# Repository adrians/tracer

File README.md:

# Electronic tracer

## The "driver-v1" folder

* Use it for physical tracer board, version 1.
* Prerequisites: `libudev1` and `g++` installed (`sudo apt-get install libudev1 build-essential`).
* Driver based on Kerry Wong's library (<https://github.com/kerrydwong/MCP2210-Library>).
* To build the driver-application, run `cd driver-v1; make`. It will generate the `tracer` binary, which should be run as root (or with the `setuid` bit set).

## The "driver-mock" folder

* Use it for local testing, without a tracer board. It's a dummy data source.
* Prerequisites: `g++` installed.
* To build it, run `cd driver-mock; make`. It will generate the `tracer` binary.

## The "frontend" directory

* Frontend done using electron.js and apex charts.
* It uses `npm`.
* To build, run `npm install`.
* To run, copy the `tracer` binary (from either `driver-v1` or `driver-mock` directories), and then run `npm start`.
* Tested with node 14.x.

The `driver-v1` requires setuid permissions. See the snippet below.

```bash
cd frontend
cp ../driver-v1/tracer .
sudo chown root tracer
sudo chmod +s tracer
npm start
```

## The "board" directory

* Contains the kicad project used for manufacturing the first iteration of the board.

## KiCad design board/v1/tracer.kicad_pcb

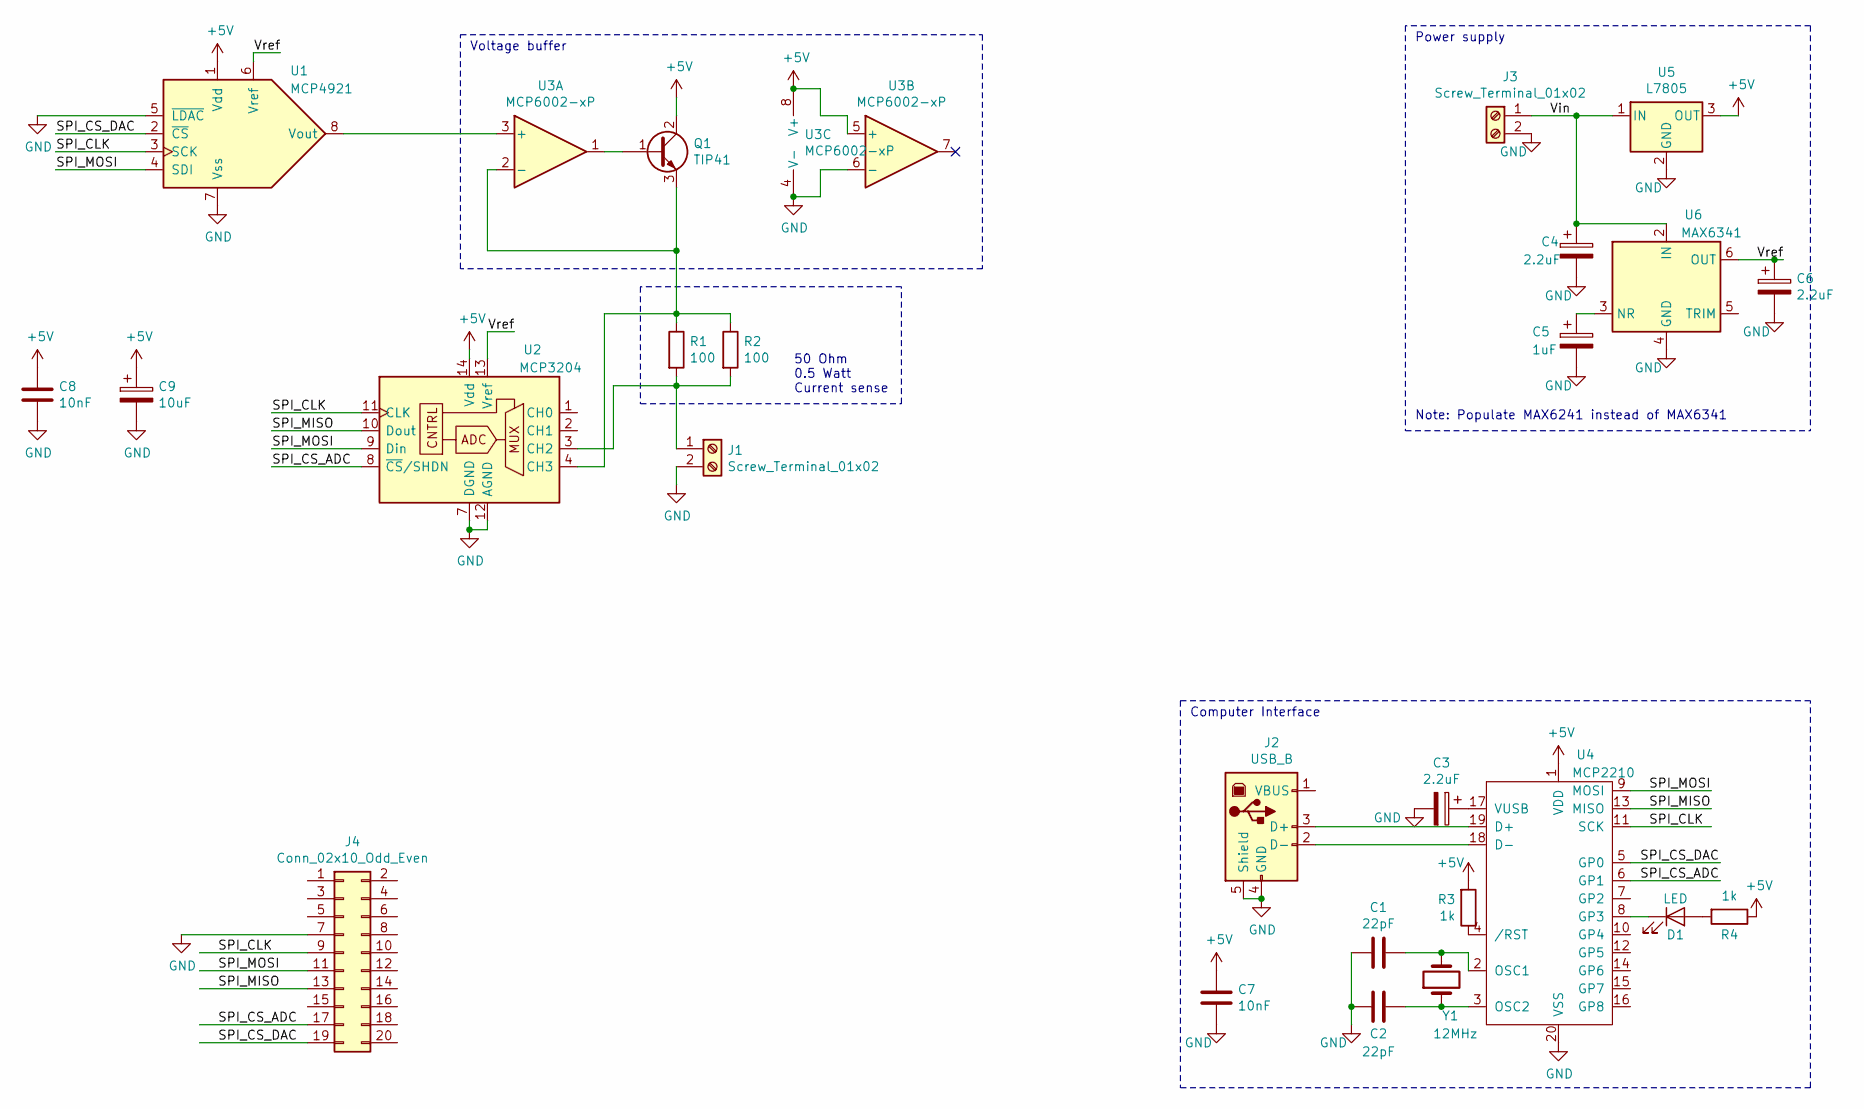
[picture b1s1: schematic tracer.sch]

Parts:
C1, C2: 22pF; C_Disc_D3.0mm_W1.6mm_P2.50mm
C3, C4, C6: 2.2uF; CP_Radial_D4.0mm_P2.00mm
C5: 1uF; CP_Radial_D4.0mm_P2.00mm
C7, C8: 10nF; C_Disc_D3.0mm_W1.6mm_P2.50mm
C9: 10uF; CP_Radial_D4.0mm_P1.50mm
D1: LED; LED_D5.0mm
J1, J3: Screw_Terminal_01x02; TerminalBlock_Phoenix_MKDS-3-2-5.08_1x02_P5.08mm_Horizontal
J2: USB_B; USB_B_OST_USB-B1HSxx_Horizontal
J4: Conn_02x10_Odd_Even; PinHeader_2x10_P2.54mm_Vertical
Q1: TIP41; TO-220-3_Horizontal_TabDown
R1, R2: 100; R_Axial_DIN0207_L6.3mm_D2.5mm_P7.62mm_Horizontal
R3, R4: 1k; R_Axial_DIN0207_L6.3mm_D2.5mm_P7.62mm_Horizontal
U1: MCP4921; DIP-8_W7.62mm
U2: MCP3204; DIP-14_W7.62mm
U3: MCP6002-xP; DIP-8_W7.62mm
U4: MCP2210; SOIC-20W_7.5x12.8mm_P1.27mm
U5: L7805; TO-220-3_Horizontal_TabDown
U6: MAX6341; DIP-8_W7.62mm
Y1: 12MHz; Crystal_HC50_Vertical

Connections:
+5V: C7.1, C8.1, C9.1, Q1.2 (C), R3.2, R4.1, U1.1 (Vdd), U2.14 (Vdd), U3.5 (+), U3.8 (V+), U4.1 (VDD), U5.3 (OUT)
/SPI_CLK: J4.9, U1.3 (SCK), U2.11 (CLK), U4.11 (SCK)
/SPI_CS_ADC: J4.17, U2.8 (~CS~/SHDN), U4.6 (GP1)
/SPI_CS_DAC: J4.19, U1.2 (~CS), U4.5 (GP0)
/SPI_MISO: J4.13, U2.10 (Dout), U4.13 (MISO)
/SPI_MOSI: J4.11, U1.4 (SDI), U2.9 (Din), U4.9 (MOSI)
/Vin: C4.1, J3.1, U5.1 (IN), U6.2 (IN)
/Vref: C6.1, U1.6 (Vref), U2.13 (Vref), U6.6 (OUT)
GND: C1.2, C2.1, C3.2, C4.2, C5.2, C6.2, C7.2, C8.2, C9.2, J1.2, J2.4 (GND), J2.5 (Shield), J3.2, J4.7, U1.5 (~LDAC), U1.7 (Vss), U2.7 (DGND), U2.12 (AGND), U3.4 (V-), U3.6 (-), U4.20 (VSS), U5.2 (GND), U6.4 (GND)
unnamed: C1.1, U4.2 (OSC1), Y1.2
unnamed: C2.2, U4.3 (OSC2), Y1.1
unnamed: C3.1, U4.17 (VUSB)
unnamed: C5.1, U6.3 (NR)
unnamed: D1.1 (K), U4.8 (GP3)
unnamed: D1.2 (A), R4.2
unnamed: J1.1, R1.2, R2.2, U2.3 (CH2)
unnamed: J2.2 (D-), U4.18 (D-)
unnamed: J2.3 (D+), U4.19 (D+)
unnamed: Q1.1 (B), U3.1
unnamed: Q1.3 (E), R1.1, R2.1, U2.4 (CH3), U3.2 (-)
unnamed: R3.1, U4.4 (/RST)
unnamed: U1.8 (Vout), U3.3 (+)

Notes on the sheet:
Power supply
Note: Populate MAX6241 instead of MAX6341
Computer Interface
50 Ohm 0.5 Watt Current sense
Voltage buffer

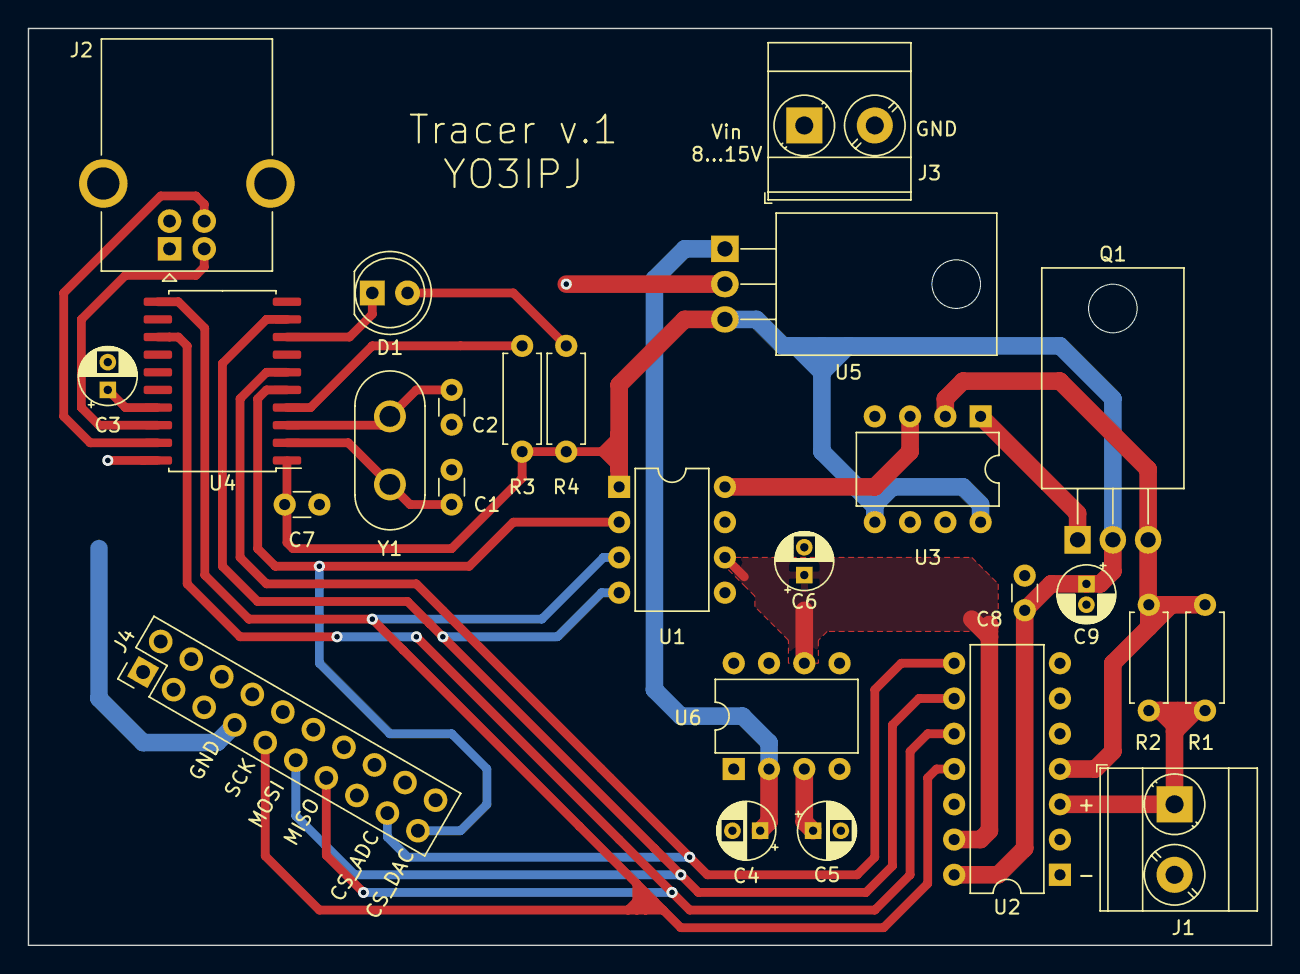
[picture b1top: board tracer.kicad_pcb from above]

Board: 2 copper layers, 89.5 x 66.0 mm, 26 parts (0 on the bottom side), 22 nets.

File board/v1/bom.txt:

22pF, 2buc, C1 C2,      https://ro.farnell.com/vishay/k220j15c0gf53l2/cap-22pf-50v-5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
10nF, 2buc, C7 C8,      https://ro.farnell.com/multicomp/mc0805y103m500a5-08mm/cap-0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
1uF, 1buc, C5,          https://ro.farnell.com/multicomp/mcnp35v105m5x11/cap-1-f-35v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
2.2uF, 3buc, C3 C4 C6,  https://ro.farnell.com/multicomp/mcksk100m2r2d11s/cap-2-2-f-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
10uF, 1buc, C9,         https://ro.farnell.com/multicomp/mcgpr16v106m5x11/cap-10-f-1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

led5mm, 1buc, D1,       https://ro.farnell.com/multicomp/mcl053pd/led-5mm-36-hi-red/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

100R, 2buc, R1 R2,      https://ro.farnell.com/multicomp/mf25-100r/res-100r-1-250mw-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
1k, 2buc, R3 R4,        https://ro.farnell.com/multicomp/mcf-0-25w-1k/res-1k-5-250mw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

12MHz xtal, Y1, 1buc,   https://ro.farnell.com/qantek-technology-corporation/qcl12-0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

terminal 2way 5.08pitch, 2buc, J1 J3,        https://ro.farnell.com/wago/235-402-331-000/terminal-block-w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

USB B, J2, 1buc,    https://ro.farnell.com/multicomp/usb-b-s-ra/usb-2-0-type-b-r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

NPN, Q1, 1buc,      https://ro.farnell.com/stmicroelectronics/tip50/transistor-n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
7805, U5, 1buc,     https://ro.farnell.com/stmicroelectronics/l7805cv/ic-v-reg-5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

MCP2210 SOIC, U4, 1buc,     https://ro.farnell.com/microchip/mcp2210-i-so/ic-usb-to-spi-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
MCP4921, U1, 1buc,  https://ro.farnell.com/microchip/mcp4921-e-p/12bit-dac-singl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
MCP3204, U2, 1buc,  https://ro.farnell.com/microchip/mcp3204-ci-p/ic-12bit-adc-3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
MCP6002, U3, 1buc,  https://ro.farnell.com/microchip/mcp6002-i-p/ic-op-amp-1-8v-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
MAX6241, U6, 1buc,  https://ro.farnell.com/maxim-integrated-products/max6241bcpa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

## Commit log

2020-01-12 Add license
2020-01-12 minor cleanup
2020-01-12 Reference local apexcharts.min.js file, fix #5
2020-01-12 driver: document prerequisites
2020-01-18 frontend: bump npm dependencies
2020-01-18 frontend: refactor, reduce duplicate code
2020-01-18 minor fixes
2020-01-18 frontend: add a textarea with raw data
2020-02-15 frontend: improve design
2020-02-15 frontend: npm update
2020-02-15 doc: add screenshot
2020-02-15 driver: add dummy data source, fix #12
2020-07-07 build(deps): bump electron from 8.2.0 to 8.2.4 in /frontend
    Bumps [electron](https://github.com/electron/electron) from 8.2.0 to 8.2.4.
    - [Release notes](https://github.com/electron/electron/releases)
    - [Changelog](https://github.com/electron/electron/blob/master/docs/breaking-changes.md)
    - [Commits](https://github.com/electron/electron/compare/v8.2.0...v8.2.4)
2020-07-19 build(deps): bump lodash from 4.17.15 to 4.17.19 in /frontend
    Bumps [lodash](https://github.com/lodash/lodash) from 4.17.15 to 4.17.19.
    - [Release notes](https://github.com/lodash/lodash/releases)
    - [Commits](https://github.com/lodash/lodash/compare/4.17.15...4.17.19)
2020-10-06 build(deps): bump electron from 8.4.0 to 8.5.1 in /frontend
    Bumps [electron](https://github.com/electron/electron) from 8.4.0 to 8.5.1.
    - [Release notes](https://github.com/electron/electron/releases)
    - [Changelog](https://github.com/electron/electron/blob/master/docs/breaking-changes.md)
    - [Commits](https://github.com/electron/electron/compare/v8.4.0...v8.5.1)
2020-10-06 build(deps): bump electron from 8.4.0 to 8.5.2 in /frontend
    Bumps [electron](https://github.com/electron/electron) from 8.4.0 to 8.5.2.
    - [Release notes](https://github.com/electron/electron/releases)
    - [Changelog](https://github.com/electron/electron/blob/master/docs/breaking-changes.md)
    - [Commits](https://github.com/electron/electron/compare/v8.4.0...v8.5.2)
2020-12-12 build(deps): bump ini from 1.3.5 to 1.3.8 in /frontend
    Bumps [ini](https://github.com/isaacs/ini) from 1.3.5 to 1.3.8.
    - [Release notes](https://github.com/isaacs/ini/releases)
    - [Commits](https://github.com/isaacs/ini/compare/v1.3.5...v1.3.8)
2021-01-05 frontend: fix #20
2021-05-10 build(deps): bump lodash from 4.17.20 to 4.17.21 in /frontend
    Bumps [lodash](https://github.com/lodash/lodash) from 4.17.20 to 4.17.21.
    - [Release notes](https://github.com/lodash/lodash/releases)
    - [Commits](https://github.com/lodash/lodash/compare/4.17.20...4.17.21)
2021-05-16 build(deps): bump apexcharts from 3.14.0 to 3.24.0 in /frontend
    Bumps [apexcharts](https://github.com/apexcharts/apexcharts.js) from 3.14.0 to 3.24.0.
    - [Release notes](https://github.com/apexcharts/apexcharts.js/releases)
    - [Commits](https://github.com/apexcharts/apexcharts.js/commits)
2021-06-10 build(deps): bump normalize-url from 4.5.0 to 4.5.1 in /frontend
    Bumps [normalize-url](https://github.com/sindresorhus/normalize-url) from 4.5.0 to 4.5.1.
    - [Release notes](https://github.com/sindresorhus/normalize-url/releases)
    - [Commits](https://github.com/sindresorhus/normalize-url/commits)
    ---
    updated-dependencies:
    - dependency-name: normalize-url
2021-10-12 build(deps): bump electron from 11.4.6 to 11.5.0 in /frontend
    Bumps [electron](https://github.com/electron/electron) from 11.4.6 to 11.5.0.
    - [Release notes](https://github.com/electron/electron/releases)
    - [Changelog](https://github.com/electron/electron/blob/main/docs/breaking-changes.md)
    - [Commits](https://github.com/electron/electron/compare/v11.4.6...v11.5.0)
    ---
    updated-dependencies:
2022-03-25 build(deps): bump electron from 11.5.0 to 13.6.6 in /frontend
    Bumps [electron](https://github.com/electron/electron) from 11.5.0 to 13.6.6.
    - [Release notes](https://github.com/electron/electron/releases)
    - [Changelog](https://github.com/electron/electron/blob/main/docs/breaking-changes.md)
    - [Commits](https://github.com/electron/electron/compare/v11.5.0...v13.6.6)
    ---
    updated-dependencies:
2022-03-26 build(deps): bump minimist from 1.2.5 to 1.2.6 in /frontend
    Bumps [minimist](https://github.com/substack/minimist) from 1.2.5 to 1.2.6.
    - [Release notes](https://github.com/substack/minimist/releases)
    - [Commits](https://github.com/substack/minimist/compare/1.2.5...1.2.6)
    ---
    updated-dependencies:
    - dependency-name: minimist
2022-06-17 build(deps): bump electron from 11.5.0 to 15.5.5 in /frontend
    Bumps [electron](https://github.com/electron/electron) from 11.5.0 to 15.5.5.
    - [Release notes](https://github.com/electron/electron/releases)
    - [Changelog](https://github.com/electron/electron/blob/main/docs/breaking-changes.md)
    - [Commits](https://github.com/electron/electron/compare/v11.5.0...v15.5.5)
    ---
    updated-dependencies:
2022-11-10 build(deps): bump electron from 11.5.0 to 18.3.7 in /frontend
    Bumps [electron](https://github.com/electron/electron) from 11.5.0 to 18.3.7.
    - [Release notes](https://github.com/electron/electron/releases)
    - [Changelog](https://github.com/electron/electron/blob/main/docs/breaking-changes.md)
    - [Commits](https://github.com/electron/electron/compare/v11.5.0...v18.3.7)
    ---
    updated-dependencies:
